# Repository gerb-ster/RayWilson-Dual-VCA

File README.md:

# Ray Wilson's Dual VCA

Somewhere I read that you can never have enough VCA’s, and I’ve build a number of them over the years. This one is a straight up clone of a design by the late Ray Wilson from Music From Outer Space. Really nice and versatile module.

## Status: Finished

- done: first schematic & board design
- done: breadboard and test
- done: design frontpanel
- done: order PCB and build prototype

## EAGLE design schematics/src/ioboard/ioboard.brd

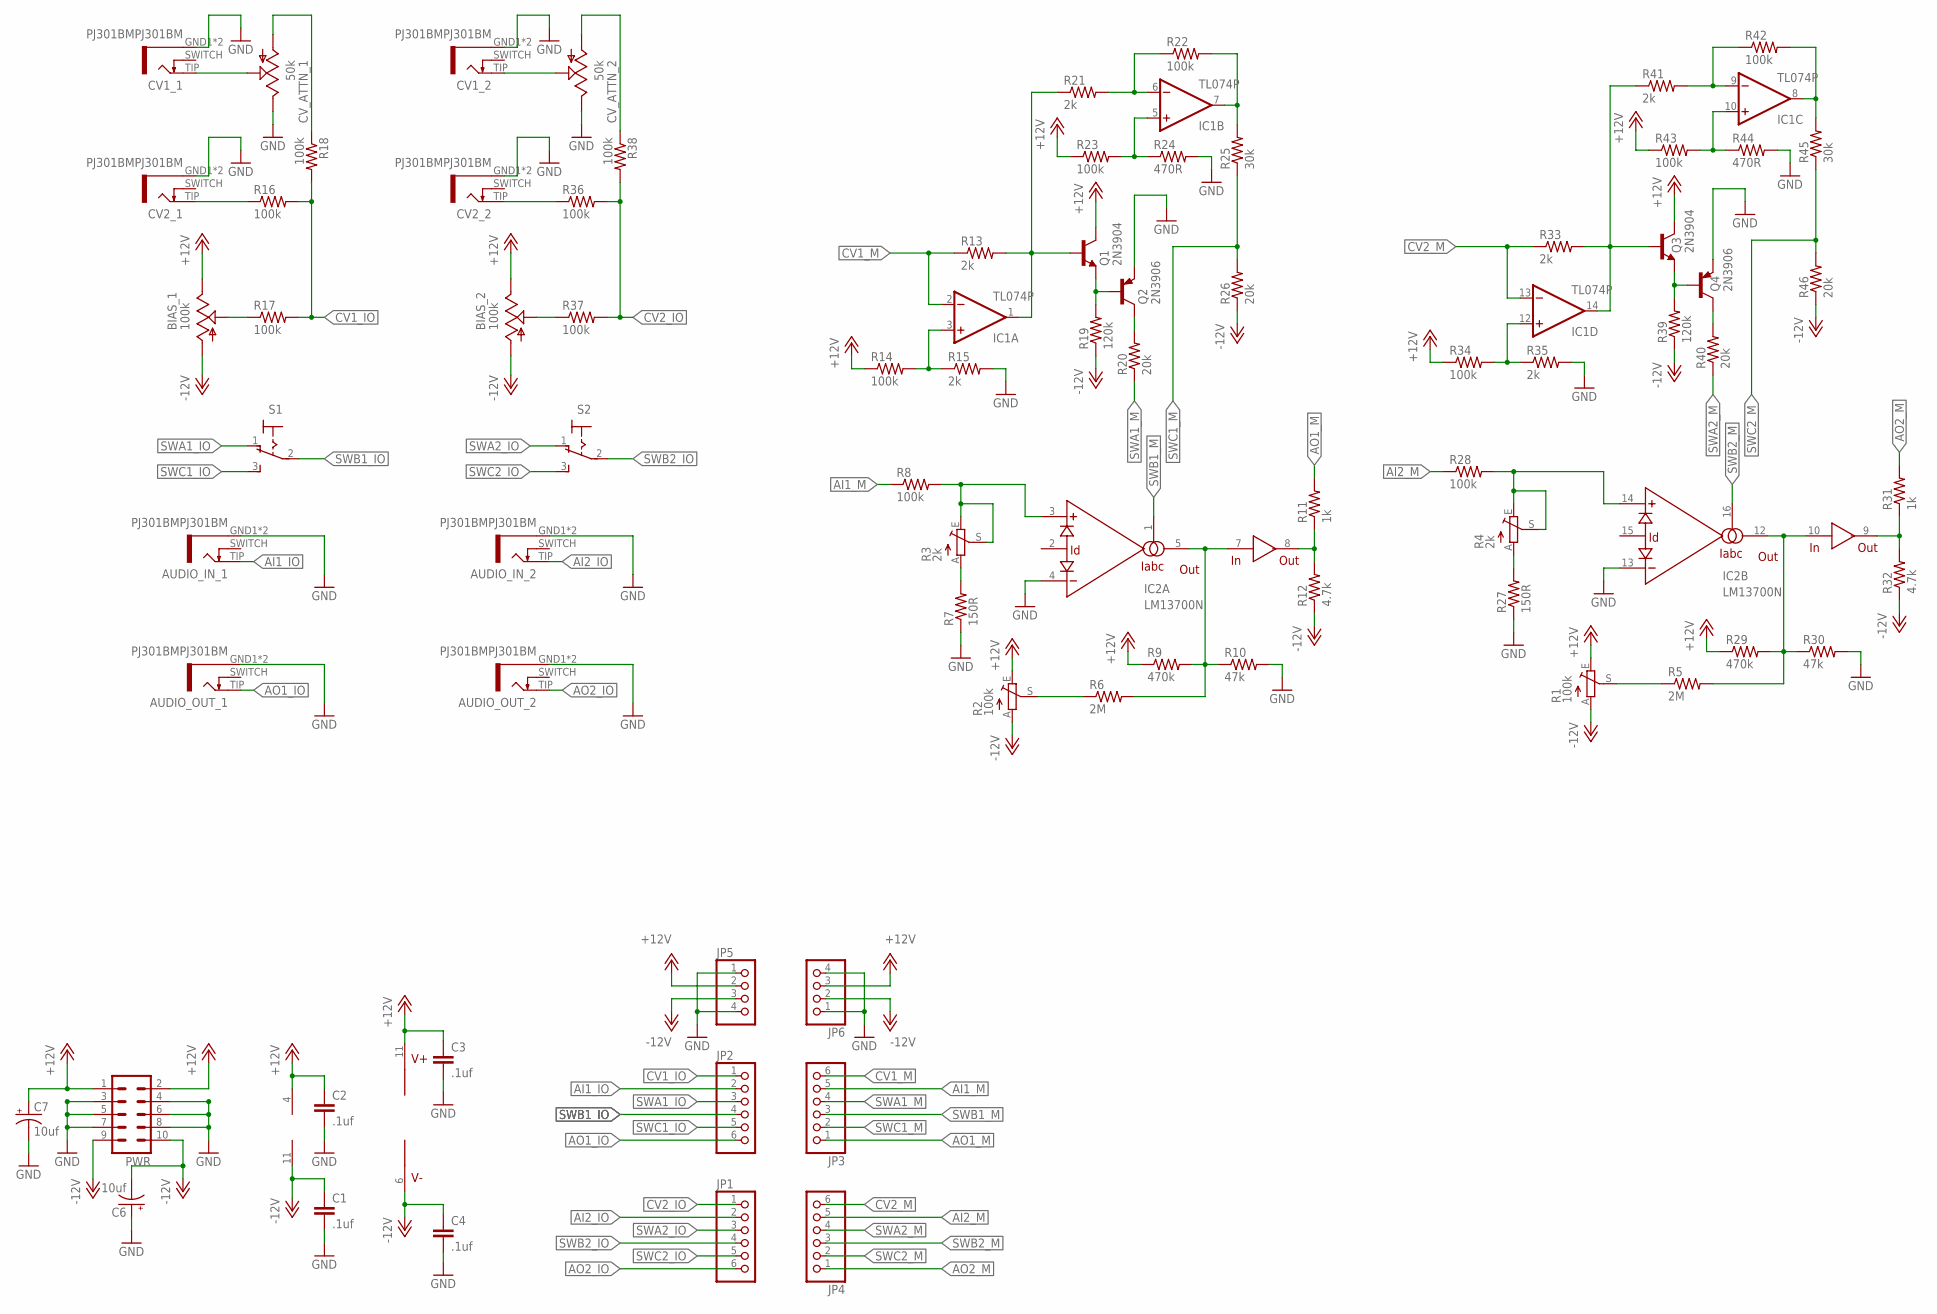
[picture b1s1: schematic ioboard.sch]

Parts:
AUDIO_IN_1, AUDIO_IN_2: PJ301BMPJ301BM; PJ301BM
AUDIO_OUT_1, AUDIO_OUT_2: PJ301BMPJ301BM; PJ301BM
BIAS_1, BIAS_2: 100k; EVUF
C1, C2, C3, C4: .1uf; C050-024X044
C6, C7: 10uf; E2,5-5
CV1_1, CV1_2, CV2_1, CV2_2: PJ301BMPJ301BM; PJ301BM
CV_ATTN_1, CV_ATTN_2: 50k; EVUF
IC1: TL074P; DIL14
IC2: LM13700N; DIL16
JP1, JP2, JP3, JP4: PINHD-1X6; 1X06
JP5, JP6: PINHD-1X4; 1X04
PWR: ML10
Q1, Q3: 2N3904; TO92
Q2, Q4: 2N3906; TO92
R1, R2: 100k; S64YW
R3, R4: 2k; S64YW
R5, R6: 2M; 0204/7
R7, R27: 150R; 0204/7
R8, R14, R16, R17, R18, R22, R23, R28, R34, R36, R37, R38, R42, R43: 100k; 0204/7
R9, R29: 470k; 0204/7
R10, R30: 47k; 0204/7
R11, R31: 1k; 0204/7
R12, R32: 4.7k; 0204/7
R13, R15, R21, R33, R35, R41: 2k; 0204/7
R19, R39: 120k; 0204/7
R20, R26, R40, R46: 20k; 0204/7
R24, R44: 470R; 0204/7
R25, R45: 30k; 0204/7
S1, S2: M9040P

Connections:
+12V: BIAS_1.3 (E), BIAS_2.3 (E), C2.1, C3.1, C7.+, IC1.4 (V+), IC2.11 (V+), JP5.2, JP6.3, PWR.1, PWR.2, Q1.1 (C), Q3.1 (C), R1.E, R2.E, R9.1, R14.1, R23.1, R29.1, R34.1, R43.1
-12V: BIAS_1.1 (A), BIAS_2.1 (A), C1.1, C4.1, C6.-, IC1.11 (V-), IC2.6 (V-), JP5.3, JP6.2, PWR.9, PWR.10, R1.A, R2.A, R12.1, R19.1, R26.1, R32.1, R39.1, R46.1
AI1_IO: AUDIO_IN_1.TIP (3), JP2.2
AI1_M: JP3.5, R8.1
AI2_IO: AUDIO_IN_2.TIP (3), JP1.2
AI2_M: JP4.5, R28.1
AO1_IO: AUDIO_OUT_1.TIP (3), JP2.6
AO1_M: JP3.1, R11.2
AO2_IO: AUDIO_OUT_2.TIP (3), JP1.6
AO2_M: JP4.1, R31.2
CV1_IO: JP2.1, R16.2, R17.2, R18.2
CV1_M: IC1.2 (-IN), JP3.6, R13.1
CV2_IO: JP1.1, R36.2, R37.2, R38.2
CV2_M: IC1.13 (-IN), JP4.6, R33.1
GND: AUDIO_IN_1.GND1 (5), AUDIO_IN_1.GND2 (5), AUDIO_IN_2.GND1 (5), AUDIO_IN_2.GND2 (5), AUDIO_OUT_1.GND1 (5), AUDIO_OUT_1.GND2 (5), AUDIO_OUT_2.GND1 (5), AUDIO_OUT_2.GND2 (5), C1.2, C2.2, C3.2, C4.2, C6.+, C7.-, CV1_1.GND1 (5), CV1_1.GND2 (5), CV1_2.GND1 (5), CV1_2.GND2 (5), CV2_1.GND1 (5), CV2_1.GND2 (5), CV2_2.GND1 (5), CV2_2.GND2 (5), CV_ATTN_1.3 (E), CV_ATTN_2.3 (E), IC2.4 (-IN), IC2.13 (-IN), JP5.1, JP5.4, JP6.1, JP6.4, PWR.3, PWR.4, PWR.5, PWR.6, PWR.7, PWR.8, Q2.3 (E), Q4.3 (E), R7.1, R10.2, R15.2, R24.2, R27.1, R30.2, R35.2, R44.2
IO_CV1: CV_ATTN_1.1 (A), R18.1
IO_CV2: CV_ATTN_2.1 (A), R38.1
unnamed: R2.S, R6.1
unnamed: R3.A, R7.2
unnamed: IC2.3 (+IN), R3.E, R3.S, R8.2
unnamed: IC2.5 (OUT), IC2.7 (IN), R6.2, R9.2, R10.1
unnamed: R4.A, R27.2
unnamed: IC2.8 (OUT), R11.1, R12.2
unnamed: BIAS_1.2 (S), R17.1
unnamed: IC1.1 (OUT), Q1.2 (B), R13.2, R21.1
unnamed: IC1.3 (+IN), R14.2, R15.1
unnamed: IC1.5 (+IN), R23.2, R24.1
unnamed: CV2_1.TIP (3), R16.1
unnamed: Q1.3 (E), Q2.2 (B), R19.2
unnamed: R1.S, R5.1
unnamed: Q2.1 (C), R20.2
unnamed: IC1.6 (-IN), R21.2, R22.1
unnamed: IC1.7 (OUT), R22.2, R25.2
unnamed: IC2.14 (+IN), R4.E, R4.S, R28.2
unnamed: IC2.10 (IN), IC2.12 (OUT), R5.2, R29.2, R30.1
unnamed: IC2.9 (OUT), R31.1, R32.2
unnamed: IC1.14 (OUT), Q3.2 (B), R33.2, R41.1
unnamed: IC1.12 (+IN), R34.2, R35.1
unnamed: Q3.3 (E), Q4.2 (B), R39.2
unnamed: Q4.1 (C), R40.2
unnamed: IC1.9 (-IN), R41.2, R42.1
unnamed: IC1.8 (OUT), R42.2, R45.2
unnamed: IC1.10 (+IN), R43.2, R44.1
unnamed: CV1_1.TIP (3), CV_ATTN_1.2 (S)
unnamed: CV1_2.TIP (3), CV_ATTN_2.2 (S)
unnamed: BIAS_2.2 (S), R37.1
unnamed: CV2_2.TIP (3), R36.1
SWA1_IO: JP2.3, S1.1 (O)
SWA1_M: JP3.4, R20.1
SWA2_IO: JP1.3, S2.1 (O)
SWA2_M: JP4.4, R40.1
SWB1_IO: JP2.4, S1.2
SWB1_M: IC2.1 (IABC), JP3.3
SWB2_IO: JP1.4, S2.2
SWB2_M: IC2.16 (IABC), JP4.3
SWC1_IO: JP2.5, S1.3 (S)
SWC1_M: JP3.2, R25.1, R26.2
SWC2_IO: JP1.5, S2.3 (S)
SWC2_M: JP4.2, R45.1, R46.2

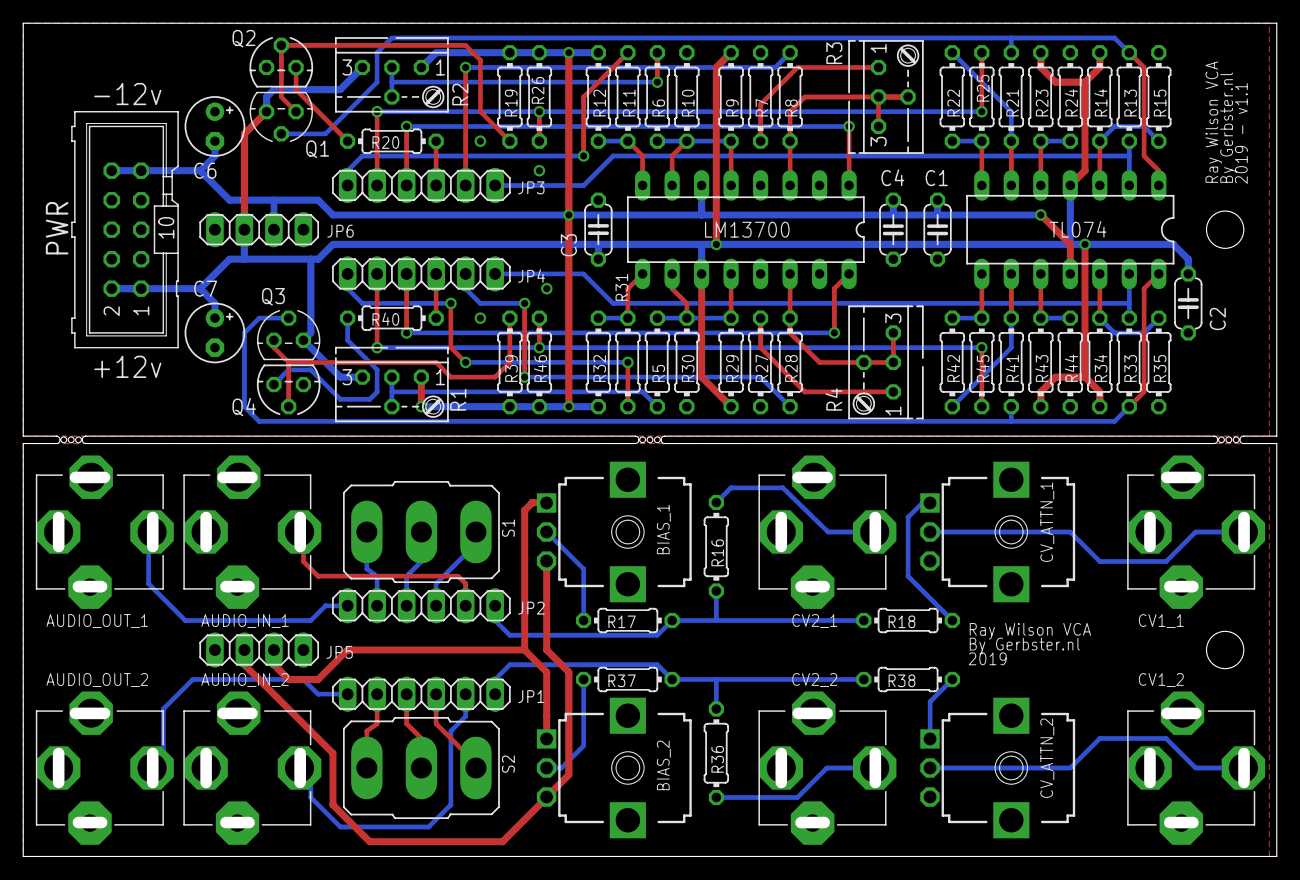
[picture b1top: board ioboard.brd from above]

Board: 2 copper layers, 108.0 x 71.8 mm, 79 parts (0 on the bottom side), 59 nets.

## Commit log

2021-05-06 some files
2021-05-07 Added files & structure
2021-05-10 Added Status
2021-05-11 Added Status & Images
2021-08-06 Updated some schematics and docs
2021-08-10 Fixed some bugs and updated documentation
2022-04-20 Some updates & bugfixes
2022-04-22 Fixed schematics & descriptions
2022-05-17 Updated Firmware
2022-05-18 Updated Faceplates
2022-05-18 Fixed issues
2022-05-21 Fixed schematics
2022-05-28 General updates
